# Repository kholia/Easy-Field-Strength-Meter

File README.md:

### Easy-Field-Strength-Meter

Jan-2022 UPDATE: v2 is published which works much better.

My old FSM build:

Testing the FSM using a common BaoFeng VHF+UHF handie:

'1N60' diodes work fine too:

Note: This particular build is using "1N60" diodes from https://www.electronicscomp.com/.
Their "1N34A Glass Type" diodes are also OK but are less sensitive.

#### Suitable Diodes

- 1N5711 diode - original from Semikart - preferred

- BAT62 Dual Schottky Diode (Detector Diode)

- "1N60" diode

- "1N34A" diode

- BAT54S - there is not much literature around this - avoid?

#### Tips

For detecting milliwatt(s) range of power, a SDR device (RTL-SDR / HackRF One /
Airspy Discovery+) works really well.

#### BOM

- 2 x 1N60 diodes *or* 1N5711 (preferred)
- 1 x 10k or 25k Potentiometer
- 2 x 0.01uF (10 nF) Non-Polar Capacitor, 500V
- 1 x LM358 (for v2)
- 1 x 100k, 1 x 2.2k Metal Film Resistors (for v2)
- 2 x Male banana plugs
- 1 x 1 or 2 inches of flexible electrical wire ("antenna")
- 1 x Wire-loop-roll works nicely for detecting HF RF power
- 2 x Few inches of PVC coated electrical wire (for connections to DMM)
- 1 x DMM
- 1 x 0.05uF Non-Polar Capacitor, 47nF is fine too (v1)
- 1 x 470pF Non-Polar Capacitor (v1)

#### BOM Sources

- https://www.semikart.com/ (BAT 62 Dual Diode - BAT62E6327HTSA1, 1N5711)

- https://projectpoint.in/ (High voltage non-polar capacitors, pots, connectors)

- https://projectpoint.in/ ("10nF 2k", "470pF 2kV", "47nF 630V")

- https://www.electronicscomp.com/ ("germanium" diodes, misc)

- https://www.electroncomponents.com/ ("germanium" diodes, misc)

- https://www.electronicscomp.com/1n34-germanium-diode-india - the displayed pic (looks like "zener") is not correct - ignore it. This actually is of "Glass Type DO-7" type.

- https://www.electronicscomp.com/1n60-germanium-diode-india?search=1n60 - this is not "glass type" but works better than their "glass type 1N34" one. This seems to be a DO-35 package.

- https://www.probots.co.in/ (project boxes/cases)

#### References

- [Radio Prepper's YouTube video - Building a Field Strength Meter.](https://www.youtube.com/watch?v=WfkNoV0a64U)

- [Schottky diodes selection guide](http://www.skoots.yolasite.com/resources/A.pdf) - superb!

- [Infineon - RF and microwave power detection with Schottky diodes](https://www.infineon.com/dgdl/Infineon-AN_1807_PL32_1808_132434_RF%20and%20microwave%20power%20detection%20-AN-v01_00-EN.pdf?fileId=5546d46265f064ff0166440727be1055) - lovely

- https://www.pasternack.com/t-calculator-power-conv.aspx (Watts to Volts)

- https://www.huyettm.net/field-strength-meter.html

- http://www.circuitdiagram.org/field-strength-meter-fsm.html

- https://www.instructables.com/id/RF-Meter-for-Multimeter/

- https://eu.mouser.com/images/vishay/images/do35.jpg

- http://www.w1air.com/images/RFDrivenOnAirIndicator.pdf (reference for v2)

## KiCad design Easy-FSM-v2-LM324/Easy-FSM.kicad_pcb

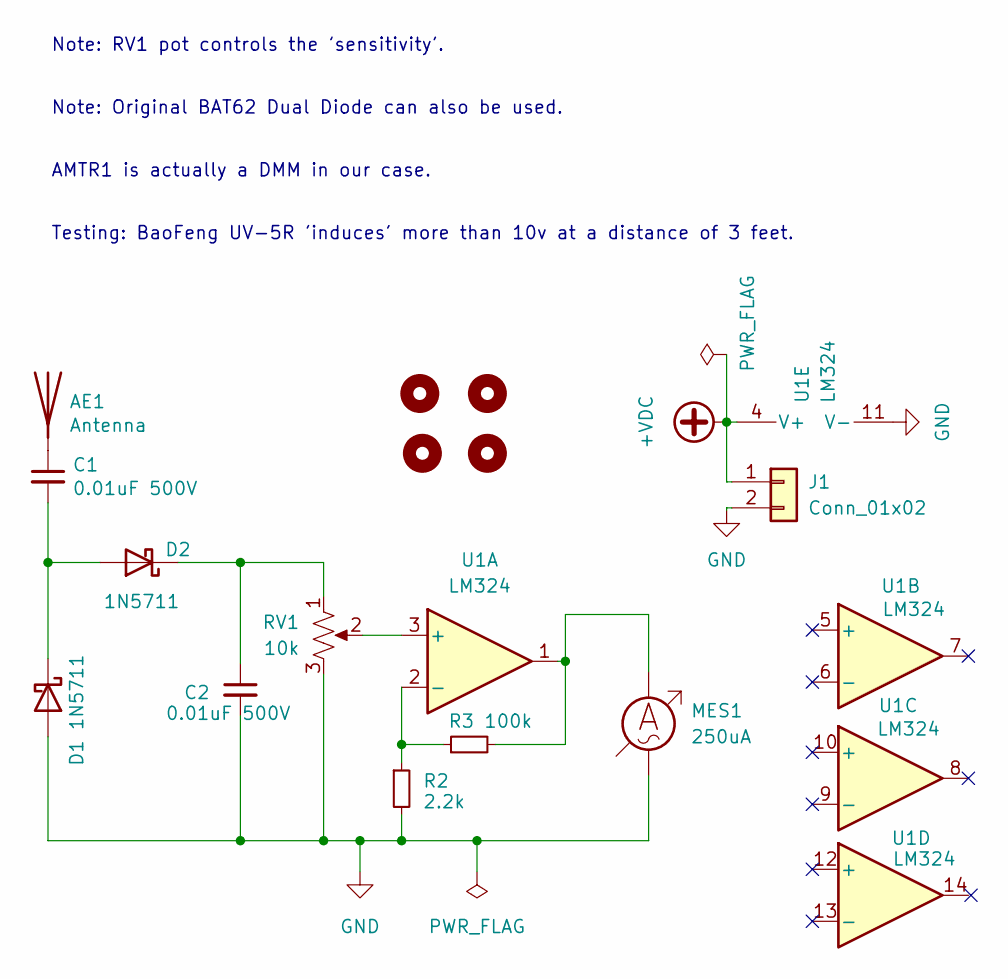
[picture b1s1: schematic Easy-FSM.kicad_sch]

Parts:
AE1: Antenna; PinSocket_1x01_P2.54mm_Vertical
C1, C2: 0.01uF 500V; C_Disc_D7.5mm_W5.0mm_P7.50mm
D1, D2: 1N5711; D_DO-35_SOD27_P7.62mm_Horizontal
H1, H2, H3, H4: MountingHole; MountingHole_2.2mm_M2
J1: Conn_01x02; PinSocket_1x02_P2.54mm_Vertical
MES1: 250uA; PinSocket_1x02_P2.54mm_Vertical
R2: 2.2k; R_Axial_DIN0207_L6.3mm_D2.5mm_P2.54mm_Vertical
R3: 100k; R_Axial_DIN0207_L6.3mm_D2.5mm_P2.54mm_Vertical
RV1: 10k; Potentiometer_Runtron_RM-065_Vertical
U1: LM324; DIP-14_W7.62mm

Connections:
+VDC: J1.1, U1.4 (V+)
GND: C2.2, D1.2 (A), J1.2, MES1.1, R2.2, RV1.3, U1.11 (V-)
unnamed: AE1.1 (A), C1.1
unnamed: C1.2, D1.1 (K), D2.2 (A)
unnamed: C2.1, D2.1 (K), RV1.1
unnamed: MES1.2, R3.2, U1.1
unnamed: R2.1, R3.1, U1.2 (-)
unnamed: RV1.2, U1.3 (+)

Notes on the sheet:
Note: RV1 pot controls the 'sensitivity'. Note: Original BAT62 Dual Diode can also be used. AMTR1 is actually a DMM in our case. Testing: BaoFeng UV-5R 'induces' more than 10v at a distance of 3 feet.

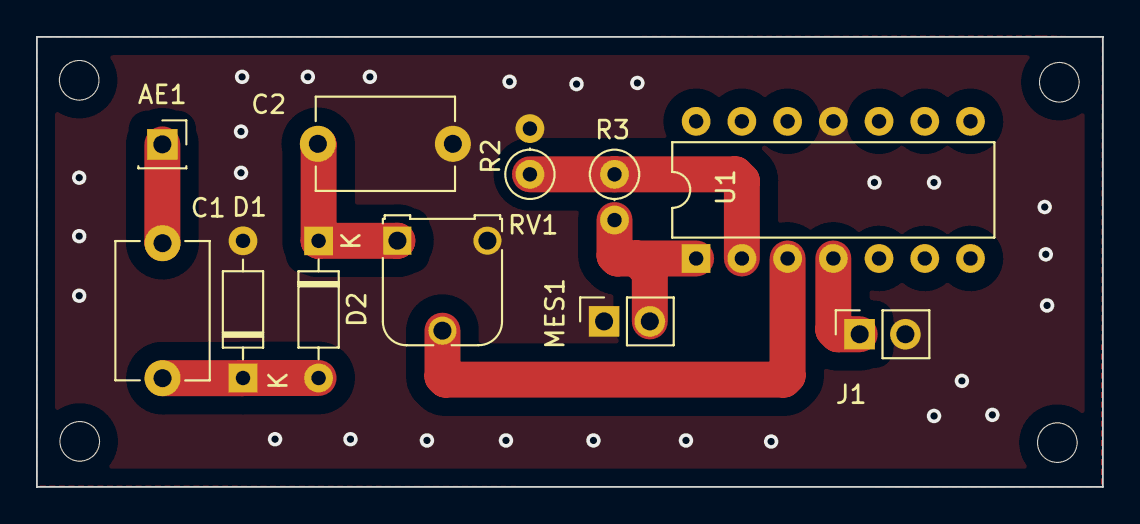
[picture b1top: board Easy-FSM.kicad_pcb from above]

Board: 2 copper layers, 59.2 x 25.0 mm, 15 parts (0 on the bottom side), 8 nets.

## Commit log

2022-02-23 Hello!
